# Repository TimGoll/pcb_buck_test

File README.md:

# Buck Test PCB

To get an understanding of different buck ICs and their drawbacks and benefits I designed this PCB. While all of them worked, some performed better than others. To verify my first impressions while initial testing I benchmarked the ICs over different voltages and currents.

_(the four different buck circuits that I tested)_

## ICs I tested

- XL1509-ADJE1 [[datasheet]](https://components.ubitap.com/datasheet/XL1509.pdf)
  - input voltage range: `4.5..40V`
  - output voltage: `1.23..37V` (fixed versions available too)
  - output current: `2A`
  - switching frequency: `50kHz/150kHz`
- MT2492 [[datasheet]](https://datasheet.lcsc.com/lcsc/1810262207_XI-AN-Aerosemi-Tech-MT2492_C89358.pdf)
  - input voltage range: `4.5..16V`
  - output voltage: `0.8..15V`
  - output current: `2A`
  - switching frequency: `600kHz`
- TPS62160DSG [[datasheet]](https://www.ti.com/lit/ds/symlink/tps62162.pdf?ts=1676897881217)
  - input voltage range: `3..17V`
  - output voltage: `0.9..6V` (fixed versions available too)
  - output current: `1A`
  - switching frequency: `2.25MHz`
  - can be used to create negative voltage

## Testing Results

### XL1509-ADJE1

_(output voltage vs different output currents)_

_(efficiency vs different output currents)_

While this IC is very cheap and has a wide range of input voltages, everything else about it isn't worth it. The low switching frequency is the reason for the huge passive components that have to be added around this IC. This negates the benefit of its price since the required components are rather expensive.

Moreover this IC really struggled with thermals. I had to stop the tests at `1750mA` due to the output becoming instable because the IC overheated.

### MT2492

_(output voltage vs different output currents)_

_(efficiency vs different output currents)_

The MT2492 is a cheap and less capable copy of the [MP2492](https://www.monolithicpower.com/en/mp2492.html) by MPS. It comes in a small package that combined with the smaller passive components needs very little space on the PCB.

Its efficiency is rather good and the output voltage is stable. Even over the time of multiple minutes the IC did not overheat when `2A` were pulled.

All in all this is a good IC when more than `1A` of continuous current is needed.

### TPS62160DSG

_(output voltage vs different output currents)_

_(efficiency vs different output currents)_

This IC made by TI is the smalles of them all. Paired with its high switching frequency the overall footprint of the circuit is really small. The output voltage is very stable, even for small drops and rather high currents. The efficiency is very good as well.

This is the best of the bunch, even though it is a bit more expensive. The most impressive thing is that it did not overheat, even though my thermal design for this circuit was very bad.

### TPS62160DSG (Inverted)

_(output voltage vs different output currents)_

_(efficiency vs different output currents)_

The same IC from the previous test was used again, but in a special configuration. With the addition of a few further passive components this IC can be used as an inverted power supply. While the input voltage range is decreased that way, the overall performance is still great.

One thing to highlight that it is possible to get stable `-5V` from a `5V` source for up to `450mA` of continous current. This makes this IC great for the use in OpAmp circuits where a negative rail is needed.

A minor drawback is that the efficiency is greatly reduced.

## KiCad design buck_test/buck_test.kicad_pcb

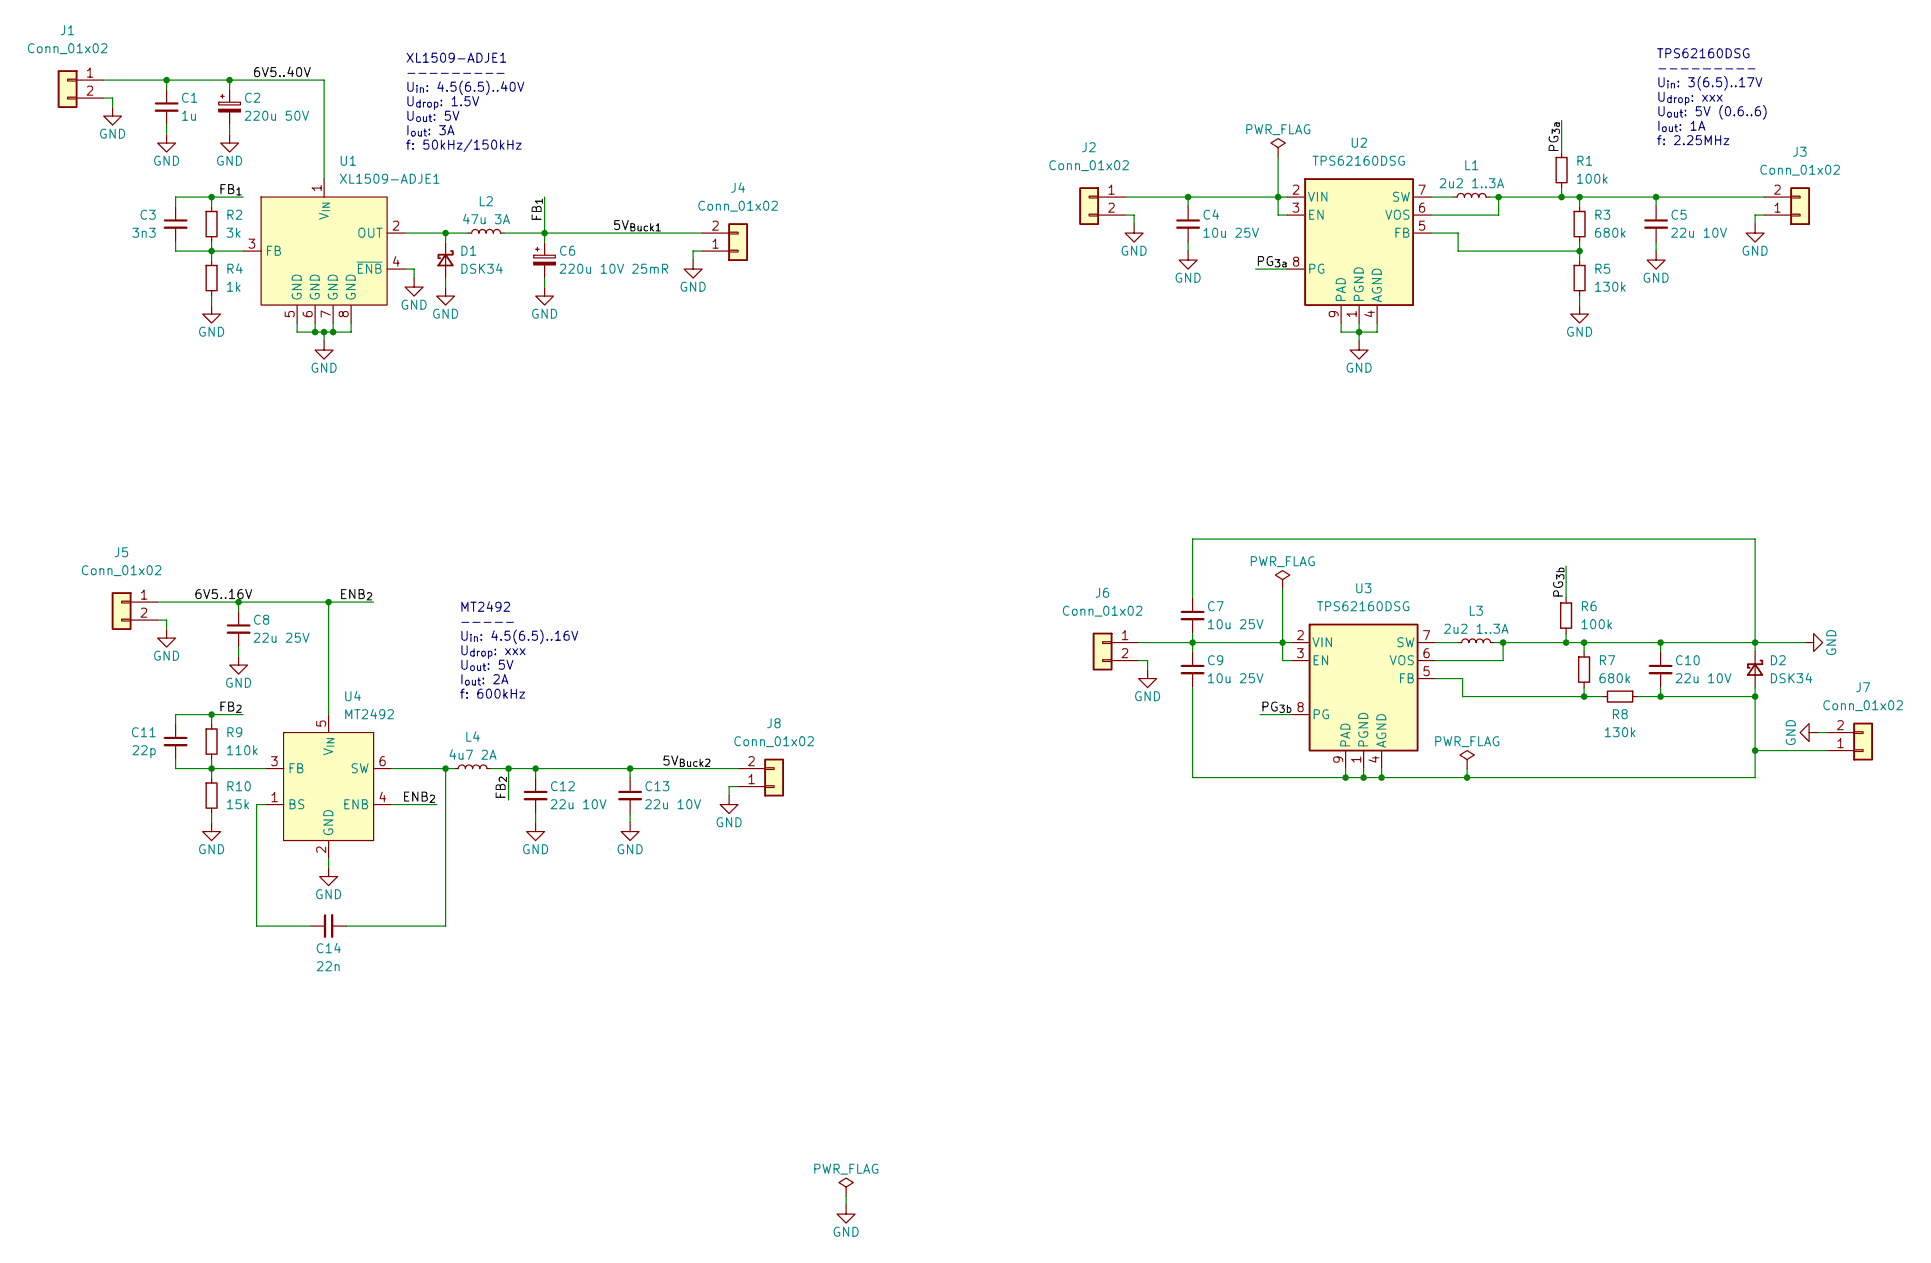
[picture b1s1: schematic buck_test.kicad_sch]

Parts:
C1: 1u; C_0603_1608Metric; LCSC Part # C15849
C2: 220u 50V; CP_Elec_10x10; LCSC Part # C125977
C3: 3n3; C_0402_1005Metric; LCSC Part # C26404
C4, C7, C9: 10u 25V; C_0603_1608Metric; LCSC Part # C96446
C5, C10, C12, C13: 22u 10V; C_1206_3216Metric; LCSC Part # C5672
C6: 220u 10V 25mR; CP_EIA-7343-31_Kemet-D; LCSC Part # C147767
C8: 22u 25V; C_0805_2012Metric; LCSC Part # C45783
C11: 22p; C_0402_1005Metric; LCSC Part # C1555
C14: 22n; C_0402_1005Metric; LCSC Part # C1532
D1, D2: DSK34; D_SOD-123; LCSC Part # C41029
J1, J2, J3, J4, J5, J6, J7, J8: Conn_01x02; TerminalBlock_Phoenix_MKDS-1,5-2-5.08_1x02_P5.08mm_Horizont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; LCSC Part # C8465
L1, L3: 2u2 1..3A; L_Wuerth_MAPI-3015; LCSC Part # C436631
L2: 47u 3A; L_12x12mm_H8mm; LCSC Part # C2983069
L4: 4u7 2A; L_Wuerth_WE-PD2-Typ-MS; LCSC Part # C354596
R1, R6: 100k; R_0603_1608Metric; LCSC Part # C25803
R2: 3k; R_0603_1608Metric; LCSC Part # C4211
R3, R7: 680k; R_0603_1608Metric; LCSC Part # C25822
R4: 1k; R_0603_1608Metric; LCSC Part # C21190
R5, R8: 130k; R_0603_1608Metric; LCSC Part # C22795
R9: 110k; R_0603_1608Metric; LCSC Part # C25805
R10: 15k; R_0603_1608Metric; LCSC Part # C22809
U1: XL1509-ADJE1; SOIC-8_3.9x4.9mm_P1.27mm; LCSC Part # C2681227
U2, U3: TPS62160DSG; WSON-8-1EP_2x2mm_P0.5mm_EP0.9x1.6mm_ThermalVias; LCSC Part # C324077
U4: MT2492; SOT-23-6; LCSC Part # C89358

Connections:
/5V_{Buck1}: C3.1, C6.1, J4.2, L2.2, R2.1
/5V_{Buck2}: C11.1, C12.1, C13.1, J8.2, L4.2, R9.1
/6V5..16V: C8.1, J5.1, U4.4 (ENB), U4.5 (V_{IN})
/6V5..40V: C1.1, C2.1, J1.1, U1.1 (V_{IN})
/PG_{3a}: R1.1, U2.8 (PG)
/PG_{3b}: R6.1, U3.8 (PG)
GND: C1.2, C2.2, C4.2, C5.2, C6.2, C7.1, C8.2, C10.1, C12.2, C13.2, D1.2 (A), D2.1 (K), J1.2, J2.2, J3.1, J4.1, J5.2, J6.2, J7.2, J8.1, L3.2, R4.2, R5.2, R6.2, R7.1, R10.2, U1.4 (~ENB), U1.5 (GND), U1.6 (GND), U1.7 (GND), U1.8 (GND), U2.1 (PGND), U2.4 (AGND), U2.9 (PAD), U3.6 (VOS), U4.2 (GND)
unnamed: C3.2, R2.2, R4.1, U1.3 (FB)
unnamed: C4.1, J2.1, U2.2 (VIN), U2.3 (EN)
unnamed: C5.1, J3.2, L1.2, R1.2, R3.1, U2.6 (VOS)
unnamed: C7.2, C9.1, J6.1, U3.2 (VIN), U3.3 (EN)
unnamed: C9.2, C10.2, D2.2 (A), J7.1, R8.1, U3.1 (PGND), U3.4 (AGND), U3.9 (PAD)
unnamed: C11.2, R9.2, R10.1, U4.3 (FB)
unnamed: C14.1, U4.1 (BS)
unnamed: C14.2, L4.1, U4.6 (SW)
unnamed: D1.1 (K), L2.1, U1.2 (OUT)
unnamed: L1.1, U2.7 (SW)
unnamed: L3.1, U3.7 (SW)
unnamed: R3.2, R5.1, U2.5 (FB)
unnamed: R7.2, R8.2, U3.5 (FB)

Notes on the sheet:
XL1509-ADJE1 --------- U_{in}: 4.5(6.5)..40V U_{drop}: 1.5V U_{out}: 5V I_{out}: 3A f: 50kHz/150kHz
TPS62160DSG --------- U_{in}: 3(6.5)..17V U_{drop}: xxx U_{out}: 5V (0.6..6) I_{out}: 1A f: 2.25MHz
MT2492 ----- U_{in}: 4.5(6.5)..16V U_{drop}: xxx U_{out}: 5V I_{out}: 2A f: 600kHz

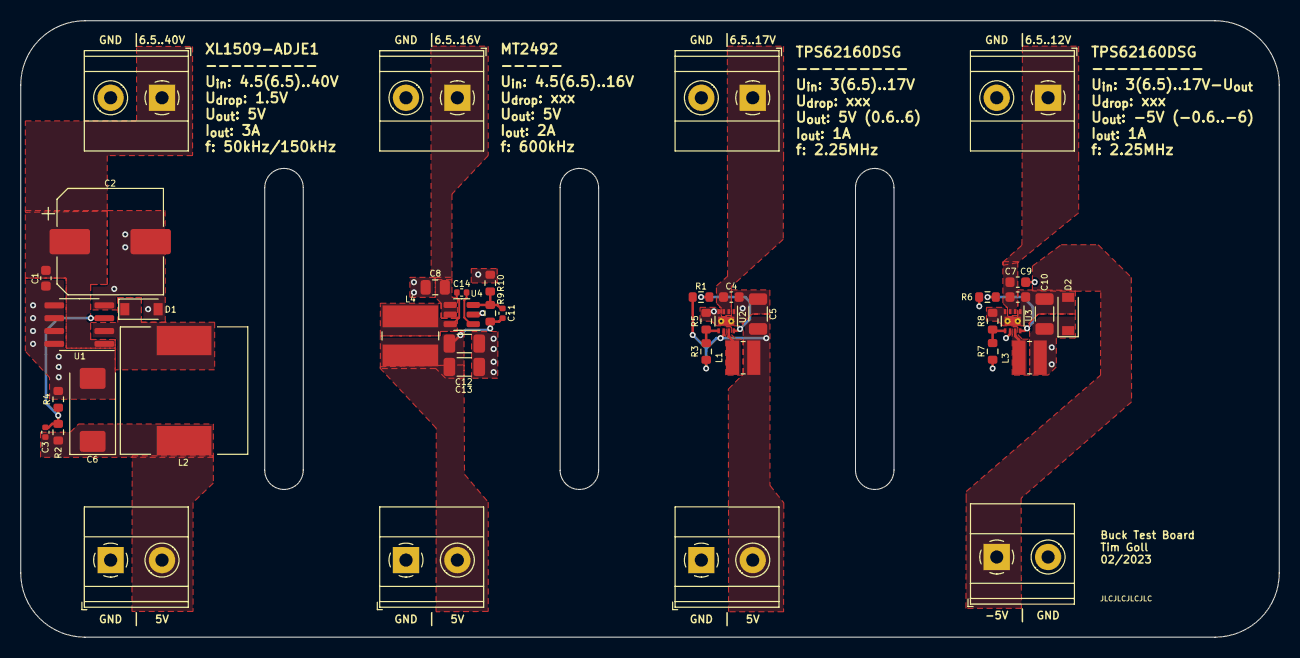
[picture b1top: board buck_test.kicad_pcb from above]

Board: 4 copper layers, 124.5 x 61.0 mm, 42 parts (0 on the bottom side), 20 nets.

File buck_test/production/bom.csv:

Designator,Footprint,Quantity,Value,LCSC Part #
C1,0603,1,1u,C15849
C10,1206,1,22u 10V,C5672
C11,0402,1,22p,C1555
C12,1206,1,22u 10V,C5672
C13,1206,1,22u 10V,C5672
C14,0402,1,22n,C1532
C2,CP_Elec_10x10,1,220u 50V,C125977
C3,0402,1,3n3,C26404
C4,0603,1,10u 25V,C96446
C5,1206,1,22u 10V,C5672
C6,CP_EIA-7343-31_Kemet-D,1,220u 10V 25mR,C147767
C7,0603,1,10u 25V,C96446
C8,0805,1,22u 25V,C45783
C9,0603,1,10u 25V,C96446
"D1, D2",D_SOD-123,2,DSK34,C41029
"J1, J2, J3, J4, J5, J6, J7, J8","TerminalBlock_Phoenix_MKDS-1,5-2-5.08_1x02_P5.08mm_Horizontal",8,Conn_01x02,C8465
"L1, L3",L_Wuerth_MAPI-3015,2,2u2 1..3A,C436631
L2,L_12x12mm_H8mm,1,47u 3A,C2983069
L4,L_Wuerth_WE-PD2-Typ-MS,1,4u7 2A,C354596
R1,0603,1,100k,C25803
R10,0603,1,15k,C22809
R2,0603,1,3k,C4211
R3,0603,1,680k,C25822
R4,0603,1,1k,C21190
R5,0603,1,130k,C22795
R6,0603,1,100k,C25803
R7,0603,1,680k,C25822
R8,0603,1,130k,C22795
R9,0603,1,110k,C25805
U1,SOIC-8_3.9x4.9mm_P1.27mm,1,XL1509-ADJE1,C2681227
"U2, U3",WSON-8-1EP_2x2mm_P0.5mm_EP0.9x1.6mm_ThermalVias,2,TPS62160DSG,C324077
U4,SOT-23-6,1,MT2492,C89358

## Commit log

2023-02-06 added schematic and BOM
2023-02-07 started PCB routing
2023-02-08 finished routing
2023-02-20 benchmarks and plots
2023-02-20 removed plots from ignore
2023-02-20 added documentation
2023-02-20 more docs
2023-02-21 fixed typo
2023-02-21 kicad 7 update
